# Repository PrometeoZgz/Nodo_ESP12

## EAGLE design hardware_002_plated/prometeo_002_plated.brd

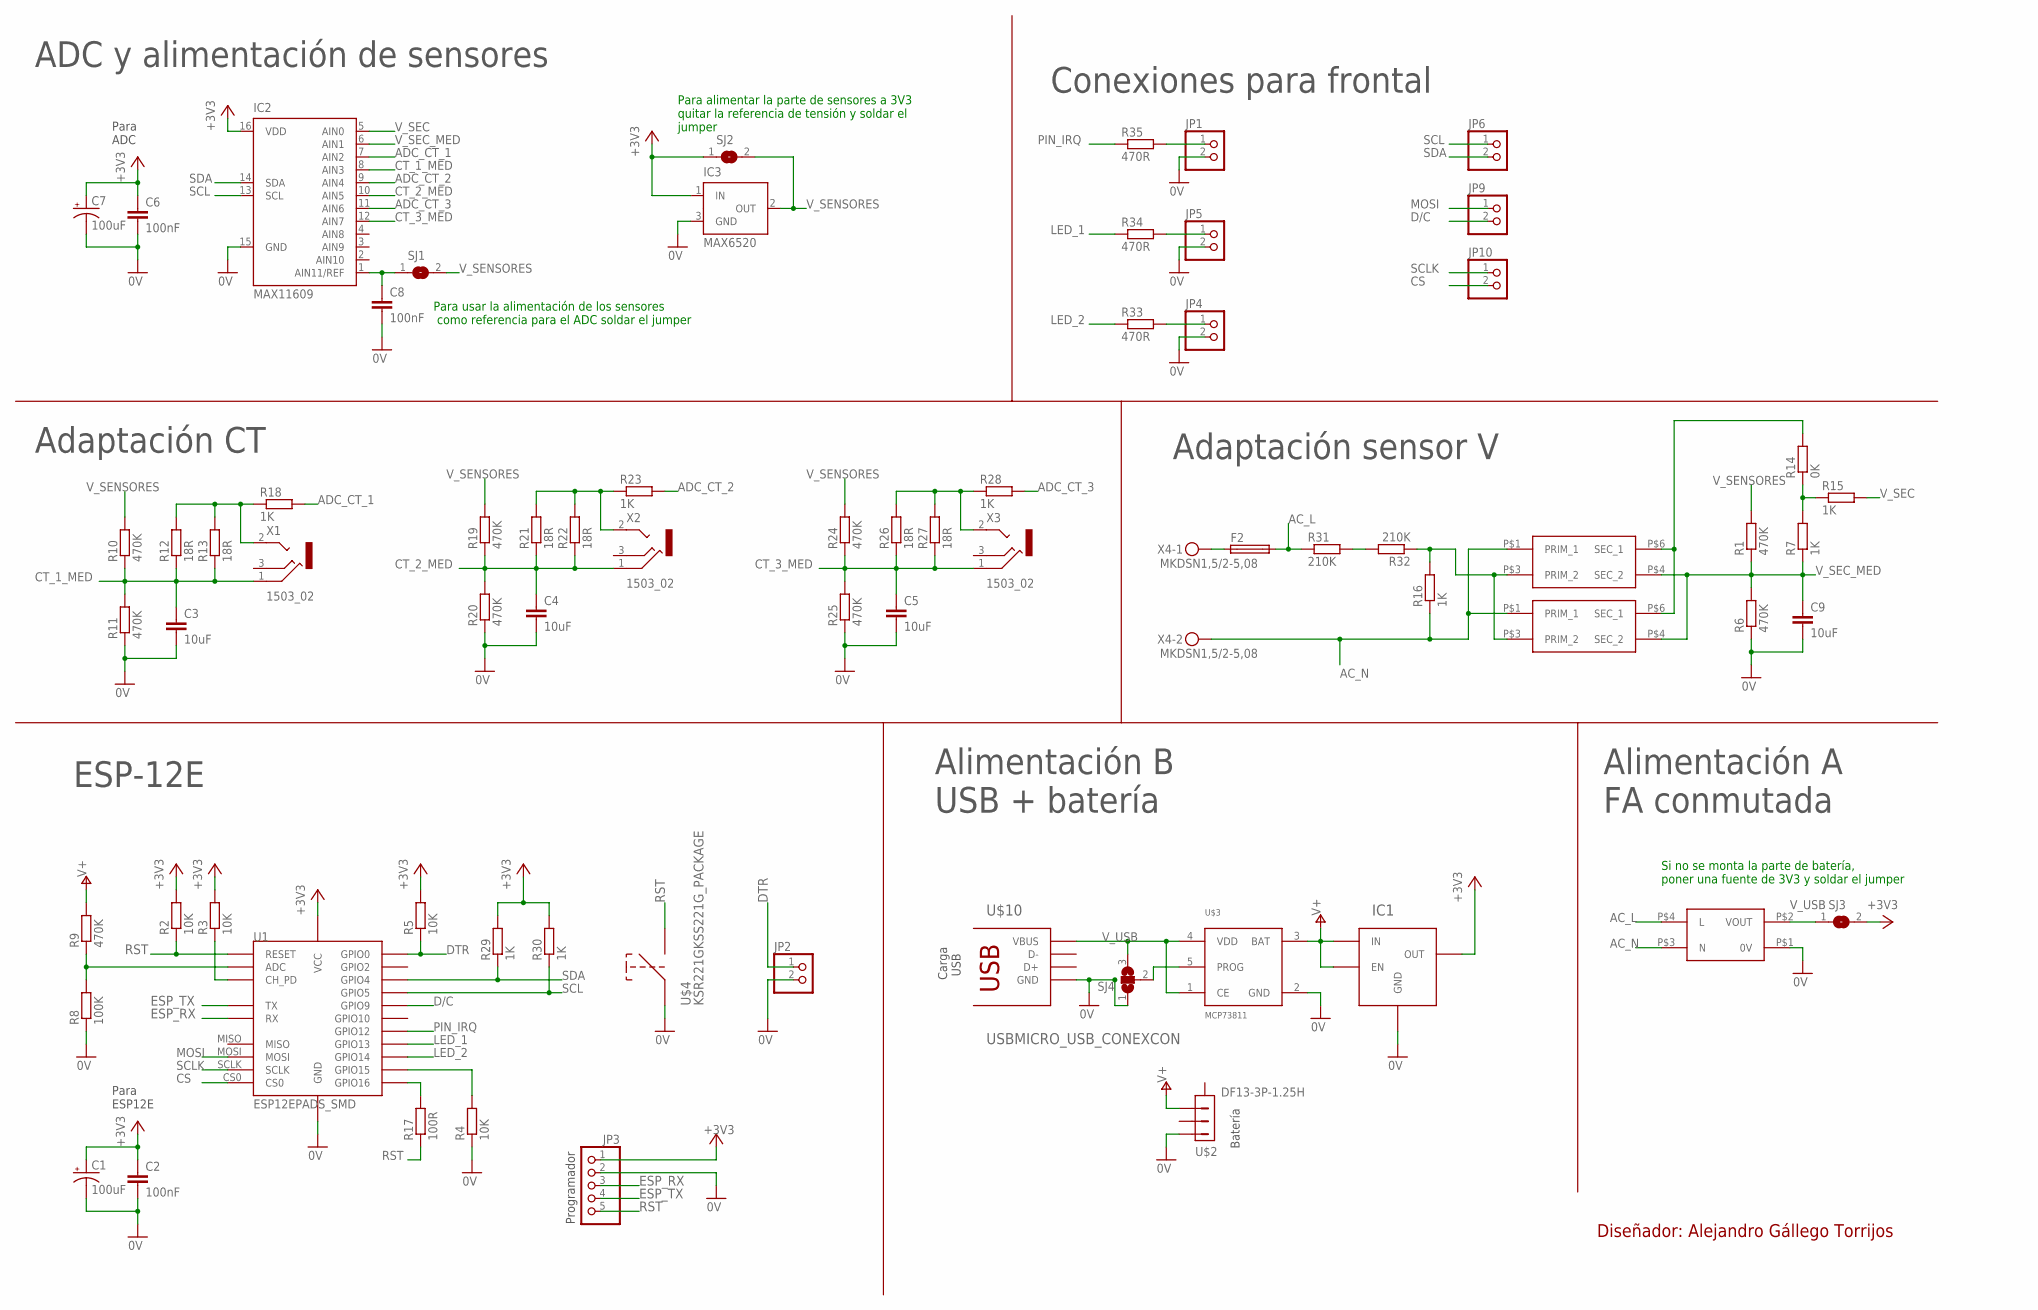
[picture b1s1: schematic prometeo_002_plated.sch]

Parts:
C1, C7: 100uF; SMC_C
C2, C6, C8: 100nF; C0402
C3, C4, C5, C9: 10uF; C0805
F2: MST 315MA 250V; TE5
IC1: STLQ015_SOT23-5L; SOT23-5L
IC2: MAX11609; QSOP16
IC3: MAX6520; SOT23
JP1, JP2, JP4, JP5, JP6, JP9, JP10: PINHD-1X2/CIRC; 1X02/CIRC
JP3: PINHD-1X5CIRC; 1X05/CIRC
R1, R6, R9, R10, R11, R19, R20, R24, R25: 470K; R0402
R2, R3, R4, R5: 10K; R0402
R7, R15, R18, R23, R28, R29, R30: 1K; R0402
R8: 100K; R0402
R12, R21, R26: 18R; R1206
R13, R22, R27: 18R; 0204/7
R14: 0K; R0402
R16: 1K; R1206
R17: 100R; R0402
R31, R32: 210K; R1206
R33, R34, R35: 470R; R0402
SJ1, SJ2, SJ3: SJ
SJ4: SJ2W; SJ_2
U1: ESP12EPADS_SMD; ESP12E_SMD
U$2: DF13-3P-1.25H; DF13A-3P-1.25H
U$3: MCP73811; SOT23-5L
U$4: KSR221GKSS221G_PACKAGE; SMD1
U$5: PSU_VTX
U$6: TRAFO_AISLAMIENTOBOURNS_SM-LP-5001; SM-LP-5001
U$7: TRAFO_AISLAMIENTOETAL_P3191; P3191
U$10: USBMICRO_USB_CONEXCON; MICROUSB_CONEXCON_5632
X1, X2, X3: 1503_02
X4: MKDSN1,5/2-5,08

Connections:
0V: C1.-, C2.2, C3.2, C4.2, C5.2, C6.2, C7.-, C8.2, C9.2, IC1.2 (GND), IC2.15 (GND), IC3.3 (GND), JP1.2, JP2.2, JP3.2, JP4.2, JP5.2, R4.1, R6.1, R8.1, R11.1, R20.1, R25.1, SJ4.1, U1.GND, U$2.P$1 (1), U$3.2 (GND), U$4.P$1, U$5.P$1 (0V), U$10.GND, U$10.GND1 (GND), U$10.GND2 (GND), U$10.P$8 (GND), U$10.P$9 (GND)
+3V3: C1.+, C2.1, C6.1, C7.+, IC1.5 (OUT), IC2.16 (VDD), IC3.1 (IN), JP3.1, R2.2, R3.2, R5.2, R29.2, R30.2, SJ2.1, SJ3.2, U1.VCC
AC_L: F2.2, R31.1, U$5.P$4 (L)
AC_N: R16.1, U$5.P$3 (N), U$6.P$1 (PRIM_1), U$7.P$1 (PRIM_1), X4.2
ADC_CT_1: IC2.7 (AIN2), R18.2
ADC_CT_2: IC2.9 (AIN4), R23.2
ADC_CT_3: IC2.11 (AIN6), R28.2
CS: JP10.2, U1.CS0
CT_1_MED: C3.1, IC2.8 (AIN3), R10.1, R11.2, R12.1, R13.1, X1.1
CT_2_MED: C4.1, IC2.10 (AIN5), R19.1, R20.2, R21.1, R22.1, X2.1
CT_3_MED: C5.1, IC2.12 (AIN7), R24.1, R25.2, R26.1, R27.1, X3.1
D/C: JP9.2, U1.GPIO9
DTR: JP2.1, R5.1, U1.GPIO0
ESP_RX: JP3.3, U1.RXD (RX)
ESP_TX: JP3.4, U1.TXD (TX)
LED_1: R34.1, U1.GPIO13
LED_2: R33.1, U1.GPIO14
MOSI: JP9.1, U1.MOSI
unnamed: R4.2, U1.GPIO15
unnamed: R16.2, R32.1, U$6.P$3 (PRIM_2), U$7.P$3 (PRIM_2)
unnamed: R3.1, U1.CH-PD (CH_PD)
unnamed: R31.2, R32.2
unnamed: R14.2, U$6.P$6 (SEC_1), U$7.P$6 (SEC_1)
unnamed: F2.1, X4.1
unnamed: R7.2, R14.1, R15.1
unnamed: SJ4.2, U$3.5 (PROG)
unnamed: JP1.1, R35.2
unnamed: R8.2, R9.1, U1.ADC
unnamed: R12.2, R13.2, R18.1, X1.2
unnamed: R17.2, U1.GPIO16
unnamed: JP4.1, R33.2
unnamed: R21.2, R22.2, R23.1, X2.2
unnamed: JP5.1, R34.2
unnamed: R26.2, R27.2, R28.1, X3.2
unnamed: C8.1, IC2.1 (AIN11/REF), SJ1.1
PIN_IRQ: R35.1, U1.GPIO12
RST: JP3.5, R2.1, R17.1, U1.RST (RESET), U$4.P$2
SCL: IC2.13 (SCL), JP6.1, R30.1, U1.GPIO5
SCLK: JP10.1, U1.SCLK
SDA: IC2.14 (SDA), JP6.2, R29.1, U1.GPIO4
V+: IC1.1 (IN), IC1.3 (EN), R9.2, U$2.P$3 (3), U$3.3 (BAT)
V_SEC: IC2.5 (AIN0), R15.2
V_SEC_MED: C9.1, IC2.6 (AIN1), R1.1, R6.2, R7.1, U$6.P$4 (SEC_2), U$7.P$4 (SEC_2)
V_SENSORES: IC3.2 (OUT), R1.2, R10.2, R19.2, R24.2, SJ1.2, SJ2.2
V_USB: SJ3.1, SJ4.3, U$3.1 (CE), U$3.4 (VDD), U$5.P$2 (VOUT), U$10.VBUS

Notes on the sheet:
Programador
Para ESP12E
ESP-12E
Carga USB
Batería
Alimentación B USB + batería
Alimentación A FA conmutada
Adaptación CT
Adaptación sensor V
Para ADC
Para alimentar la parte de sensores a 3V3 quitar la referencia de tensión y soldar el jumper
Para usar la alimentación de los sensores como referencia para el ADC soldar el jumper
Si no se monta la parte de batería, poner una fuente de 3V3 y soldar el jumper
Conexiones para frontal
Diseñador: Alejandro Gállego Torrijos
ADC y alimentación de sensores

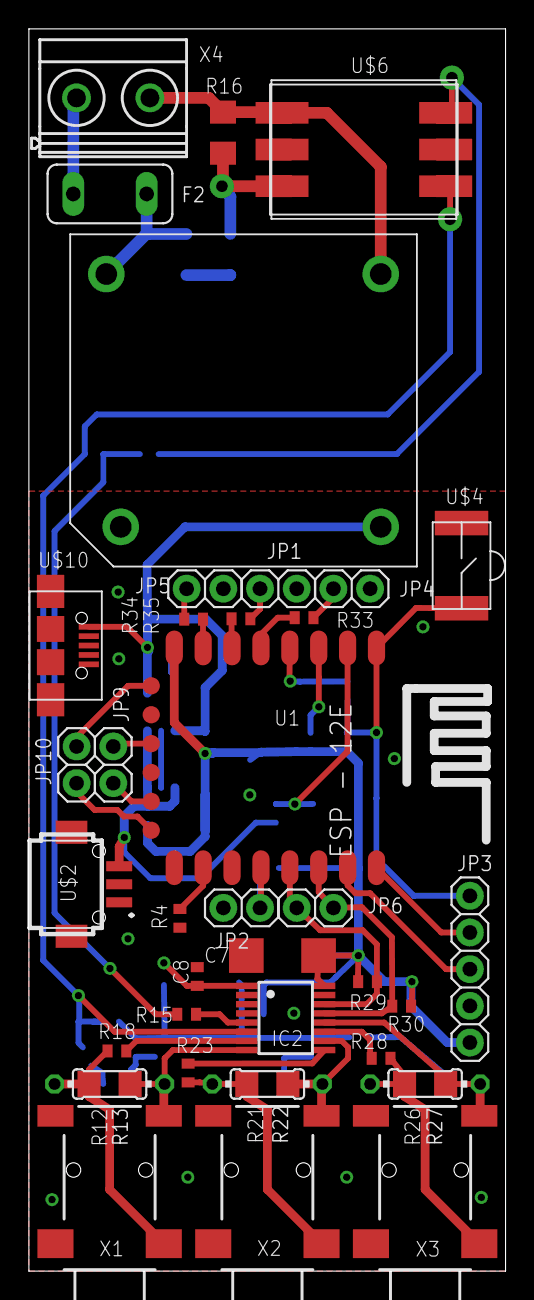
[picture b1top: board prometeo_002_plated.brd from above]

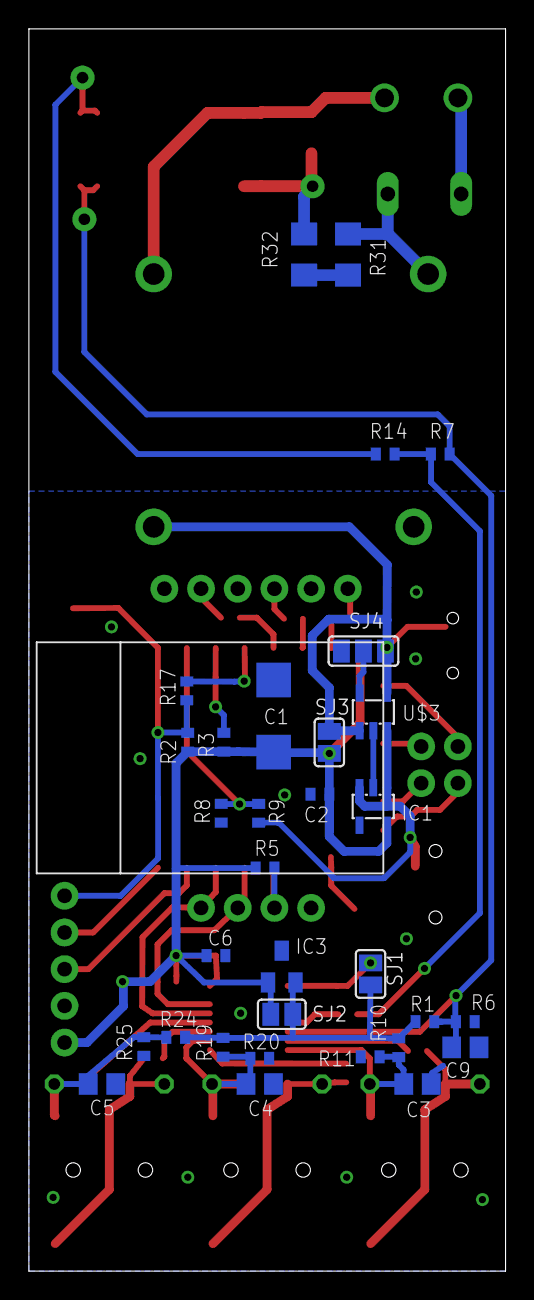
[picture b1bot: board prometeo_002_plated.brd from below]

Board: 2 copper layers, 33.0 x 86.0 mm, 72 parts (32 on the bottom side), 45 nets.

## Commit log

2017-10-24 First commit
    First commit adding the developed hardware.
2018-01-17 C7 position changed
2018-01-19 Code commit
    Added libraries for measurement
    Added basic example to check the node
2018-02-27 Added a file with the signals of each pin
